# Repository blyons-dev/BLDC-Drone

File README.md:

# BLDC-Drone
## Overview
This project is a custom-built quadcopter drone powered by four brushless DC (BLDC) motors. The system is designed around an STM32 microcontroller, which handles real-time motor control using a custom sensorless control algorithm. The goals of this project are to develop a compact and efficient drone platform with fully in-house hardware and firmware design, to explore the concept of BLDC motor control, and to fulfill my bitter regrets of not being able to make a functional drone for the 2026 Southeast Con Hardware Competition.
## Features
- STM32-based flight control system for precise and responsive operation
- Sensorless BLDC motor control (no Hall effect or other sensors required)
- Custom hardware design, including schematics and PCB layouts
- Integrated 3D models for mechanical components and assembly
## Repository Structure
- /hardware
  - Contains all physical design files for the drone:
    - KiCad schematics and PCB layouts
    - 3D models for structural and mounting components
- /software (planned, not implemented yet)
  - Will include firmware and control algorithms for the STM32, including motor control and flight logic
## Project Milestones
- Develop a reliable sensorless BLDC control system
- Design and fabricate a fully custom drone PCB
- Integrate hardware and software into a stable flight platform
- Provide a modular foundation for future improvements (ex: sensors, autonomy, communication systems)
## Status
This project is currently in active development. Hardware designs are available but are subject to change, and software development is ongoing.

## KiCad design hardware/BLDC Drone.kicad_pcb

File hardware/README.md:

# KiCAD Setup

## Installation
1. Download KiCAD from the official website.
2. Follow the installation instructions for your operating system.

## Configuration
1. Open KiCAD and open the project you'd like to use to work on the repo.
2. Initialize git in the local folder you're using and connect to GitHub.
```bash
git init
git remote add origin https://github.com/blyons-dev/BLDC-Drone.git
```
3. Switch to the current branch (replace current-branch with the branch name).
```bash
git fetch origin
git checkout -b current-branch origin/current-branch
```
4. Configure git to track the right branch.
```bash
git branch --set-upstream-to=origin/current-branch current-branch
```
4a. Optional. Verify you're on the right branch.
```bash
git branch -v
```
5. The plugin in KiCad can only be accessed in the Layout Editor, so navigate there. The plugin will automatically detect any Unstaged Changes that you have made, you just need to verify that by clicking **Rescan**.
6. Click the **Stage Changed** button to prepare everything for a commit
7. Write in the Commit Message a description of what you changed and click the **Sign Off** button as well.
8. Click **Commit** and then **Push** to send everything to the online repo.

# Project Structure

The entire project folder will be dumped here, so any resources used in the project (like custom symbols or footprints, which will be saved in project libraries) will be saved here as well.

# Version Information

- KiCAD Version: 10.0
- Last Updated: 2026-03-25

Ensure to keep your KiCAD and all libraries updated to the latest stable versions for compatibility and access to new features.

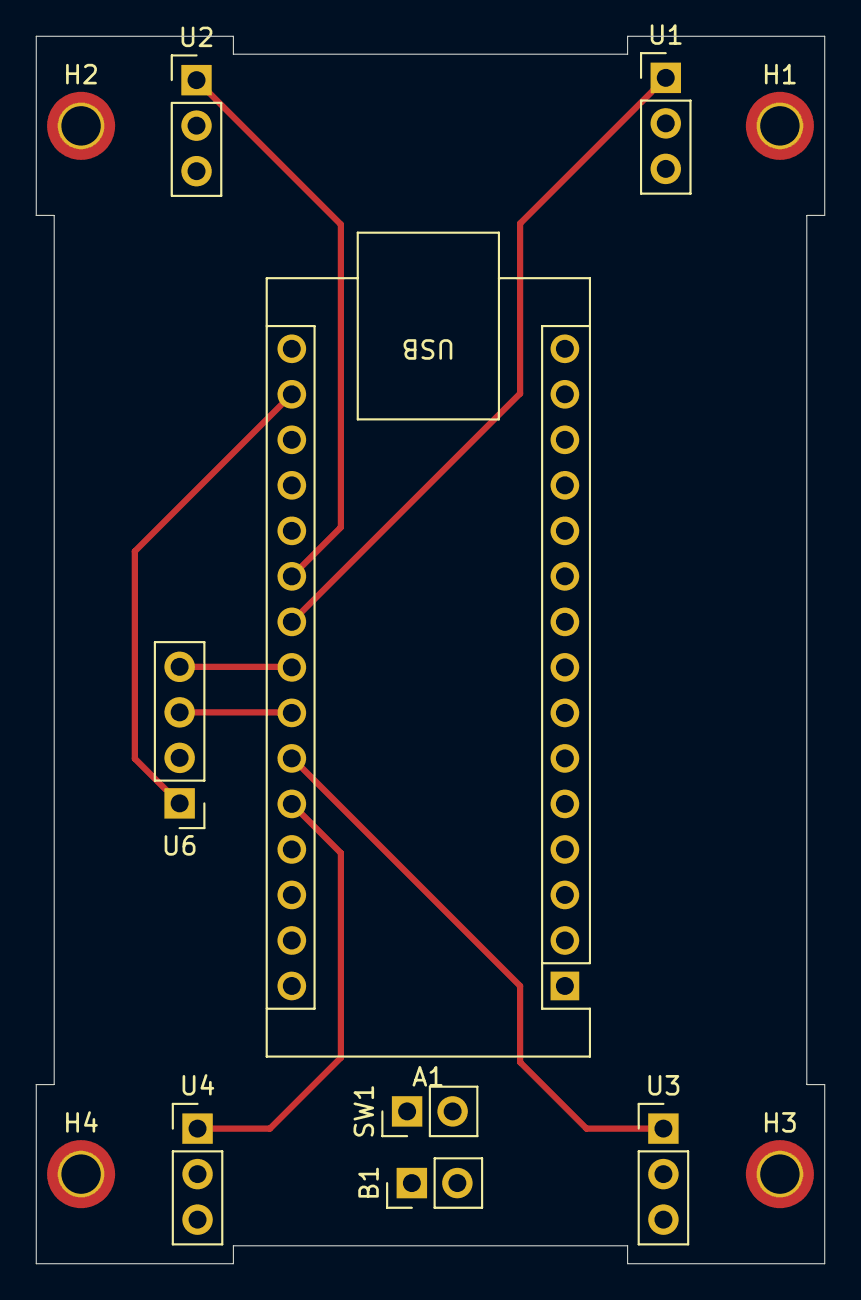
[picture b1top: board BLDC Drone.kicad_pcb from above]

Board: 2 copper layers, 44.0 x 68.5 mm, 12 parts (0 on the bottom side), 9 nets.

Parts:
A1: Arduino_Nano_ESP32; Arduino_Nano
B1: 7.6V LiPo Battery; PinHeader_1x02_P2.54mm_Vertical
H1, H2, H3, H4: MountingHole_Pad; MountingHole_2.2mm_M2_DIN965_Pad_TopBottom
SW1: SW_SPDT; PinHeader_1x02_P2.54mm_Vertical
U1, U2, U3, U4: PinHeader_1x03_P2.54mm_Vertical
U6: Gyro Header; PinHeader_1x04_P2.54mm_Vertical

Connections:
3.3V: A1.17 (3V3), U6.1
7.6V: A1.30 (VIN), SW1.2 (B), U1.2 (Vin), U2.2 (Vin), U3.2 (Vin), U4.2 (Vin)
GND: A1.4 (GND), A1.29 (GND), B1.2, H1.1, H2.1, H3.1, H4.1, U1.3 (GND), U2.3 (GND), U3.3 (GND), U4.3 (GND), U6.2
M1 PWM: A1.22 (A3), U1.1 (Throttle_Input)
M2 PWM: A1.21 (A2), U2.1 (Throttle_Input)
M3 PWM: A1.25 (A6), U3.1 (Throttle_Input)
M4 PWM: A1.26 (A7), U4.1 (Throttle_Input)
SCL: A1.24 (SCL/A5), U6.3
SDA: A1.23 (SDA/A4), U6.4

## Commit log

2026-03-23 Create .gitignore file with KiCAD exclusions
2026-03-23 Add KiCAD setup and project documentation to README.md
2026-03-23 Add files via upload
    Uploaded Arduino Version to git from files
2026-03-23 Update project description in README.md
    Clarified future plans for Arduino and STM32 versions.
2026-03-23 Enhance README description with additional details
    Updated project description to include Arduino NANO and ESC details.
2026-03-23 Revise README with project structure and KiCAD version
    Updated project structure details and added KiCAD version information.
2026-03-23 Revise README for project structure and KiCAD version
    Updated project structure description and KiCAD version.
2026-03-23 Fixed git plugin in KiCad and uploading everything from project folder into arduino branch
2026-03-23 Enhance README with KiCAD and GitHub setup instructions
    Updated README with detailed instructions for using KiCAD with GitHub, including project setup and commit process.
2026-03-23 Added gitignore into the hardware folder
    Moving the gitignore file into the hardware folder as that is where it is actually needed.
2026-03-23 Delete .gitignore
    moving the file into the hardware folder
2026-03-23 Moving the gitignore
    moving the gitignore where it is actually needed
2026-03-23 Format git commands and enhance README instructions
    Formatted git commands as code blocks and improved clarity in instructions.
2026-03-23 Enhance README with git setup instructions for KiCAD
    Added detailed instructions for initializing git and managing branches in KiCAD.
2026-03-23 "Finished" schematic for stm version
2026-03-23 fixed previous commit
2026-03-24 Enhance README with project details and structure
    Expanded project overview, features, repository structure, project milestones, and status.
2026-03-24 Expand README with detailed project overview
    This update expands the README to provide a detailed overview of the Arduino and ESC version of the BLDC Drone project, including its purpose, features, repository structure, key differences from the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
2026-03-24 Improve formatting of repository structure in README
    Reformatted the repository structure section for clarity.
2026-03-25 Updated KiCad to 10.0
2026-03-25 Enhance .gitignore for KiCad project files
    Expanded .gitignore to include additional temporary and backup file patterns for KiCad projects.
2026-03-25 Enhance .gitignore for KiCad project files
    Expanded .gitignore to include additional temporary and backup files for KiCad projects.
2026-03-25 Update KiCAD version to 10.0 and last updated date
    Updated KiCAD version and last updated date in README.
2026-03-25 Add Git plugin installation step to README
    Added instructions for installing the Git plugin for KiCAD.
